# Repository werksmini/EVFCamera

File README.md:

# EVFCamera

A compact rangefinder-style digital camera built on a Raspberry Pi Zero 2 W and the Raspberry Pi HQ camera, with C/CS-mount lenses. You compose, review and change settings entirely through a 0.4" 1280×960 micro-OLED eye-level EVF.

## Hardware

| Part | Choice |
| --- | --- |
| Computer | Raspberry Pi Zero 2 W (hostname `EVFPi`) |
| Sensor | Raspberry Pi HQ camera (Sony IMX477) |
| Viewfinder | 0.4" 1280×960 HDMI micro-OLED, 12.5× eyepiece |
| Lenses | Fujinon-TV 9 mm f/1.4, 17 mm f/1.7 (C-mount) |
| Shutter | Alps SKRNPEE010 two-stage switch (bench: 6×6 tact switch) |
| Power | Adafruit bq25185 USB-C charger + 5 V boost, 1-cell Li-ion |
| Sensors | Deferred: MAX17048 fuel gauge, VCNL4040 eye sensor (I²C pins kept free) |

## Repository layout

| Folder | Contents |
| --- | --- |
| `bench/` | Standalone test scripts used while bringing up the hardware |
| `hardware/kicad/` | Footprints and PCB files |
| `docs/` | Roadmap and design notes |

| `evfcam/` | The camera app |
| `tests/` | Mode and control tests (run anywhere with the fake camera) |
| `tools/` | Helpers, e.g. `render_screens.py` draws every screen to PNG |

See [docs/roadmap.md](docs/roadmap.md) for the architecture and milestones.

## Setup on the Pi

Raspberry Pi OS Lite (64-bit), then:

```bash
sudo apt update && sudo apt full-upgrade -y
sudo raspi-config nonint do_i2c 0
sudo apt install -y python3-picamera2 --no-install-recommends
sudo apt install -y rpicam-apps-lite python3-pil python3-evdev python3-numpy python3-gpiozero i2c-tools git

mkdir -p ~/evfpi && cd ~/evfpi
python3 -m venv --system-site-packages .venv
source .venv/bin/activate
# later, for the deferred sensors:
# pip install adafruit-blinka adafruit-circuitpython-max1704x adafruit-circuitpython-vcnl4040
git clone https://github.com/werksmini/EVFCamera.git
```

Bench monitor (Waveshare 10.4" 1600×720, mounted upside down): add to the single line in `/boot/firmware/cmdline.txt`, then reboot:

```text
video=HDMI-A-1:1600x720,rotate=180
```

For the EVF instead: `video=HDMI-A-1:1280x960@60D`.

## Running the camera app

```bash
cd ~/evfpi/EVFCamera && git pull
python3 -m evfcam            # bench monitor (flipped, 960x720 window)
python3 -m evfcam --evf      # 0.4" EVF, 1280x960, not flipped
python3 -m evfcam --fake     # no camera: work on the UI anywhere
```

At the shutter press the screen goes dark with a white border and a red dot until the photo is saved, then live view returns with "SAVED". Review after the shot and the flash itself are in Menu > Display. In Shoot mode, the EV readout turns red with "MAX" when the exposure can't get any brighter.

Controls, typed in the SSH terminal or on a keyboard plugged into the Pi:

| Key | Camera control | Shoot | Magnify | Menu (page list) | Menu (inside a page) | Playback |
| --- | --- | --- | --- | --- | --- | --- |
| Space | Shutter (full) | Take photo | Take photo | Close | Close | Close |
| `h` | Shutter (half) | – | Close | Close | Close | Close |
| Enter | OK | Magnify 5× | 10×, then off | Open page | Step value / run action | – |
| ↑ ↓ | D-pad | ISO (Manual) | – | Move | Move | – |
| ← → | D-pad | – | – | ← close, → open | Change value | Browse |
| `m` | Menu | Open menu | Close | Close | Close menu | Close |
| `p` | Play | Playback | Playback | – | – | Close |
| `b` / Backspace | Back | Reset EV | Close | Close | Up to page list | Close |
| `[` `]` | Thumb wheel | EV (A) / shutter (S, M) | – | – | Change value | Browse |
| `q` | – | Quit | Quit | Quit | Quit | Quit |

Settings are saved to `~/.config/evfcam/settings.json` and come back after a restart.

The bench shutter button on GPIO 27 also works. Photos save to `~/evfpi/photos`.

Run the tests: `python3 tests/test_modes.py`

## Bench scripts

| Script | What it does |
| --- | --- |
| `bench/preview.py` | Live preview only |
| `bench/overlay.py` | Preview with exposure info and focus meter overlay |
| `bench/camera.py` | Overlay + shutter button on GPIO 27 (header pin 13, other leg to GND pin 14); saves full-res JPEGs to `~/evfpi/photos` |

```bash
cd ~/evfpi && source .venv/bin/activate
python3 EVFCamera/bench/camera.py
```

Set `FLIP = False` at the top of a script when using the EVF instead of the flipped bench monitor.

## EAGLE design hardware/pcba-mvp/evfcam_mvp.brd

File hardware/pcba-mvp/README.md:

# MVP main board (milled, single-sided)

`python3 make_pcba.py` places every part, routes the copper, checks clearances and writes:

| File | Use |
|---|---|
| `evfcam_mvp.sch`, `evfcam_mvp.brd` | Fusion Electronics (EAGLE 9 XML). Upload both together: File > Upload, or drag into the Data Panel |
| `gerber/evfcam_mvp-B_Cu.gbr` | Bottom copper, for isolation milling (FlatCAM, Carbide Copper, Fusion PCB CAM...) |
| `gerber/evfcam_mvp-Edge_Cuts.gbr` | Board outline and camera ribbon slot |
| `gerber/evfcam_mvp-PTH.drl`, `-NPTH.drl` | Pin holes (0.9 / 1.0 / 1.2 / 1.4 / 1.5 mm) and M2.5 screw holes (2.75 mm) |
| `preview.png` | Component side and the mirrored copper side |
| `fusion_dummy_board.py` | "Dummy board (print)" sketch: outline, cut-out and every hole, sizes as Fusion parameters |
| `fusion_sketches.py`, `layout.json` | Draws the layout into the Fusion "PCBA" design (`make_fusion_script.py` rebuilds it) |

Needs `numpy scipy scikit-image pillow shapely`.

## Board

Layout follows the "Skeleton" sketch in the Fusion PCBA design (105 x 55 mm, Pi in the bottom-left
corner), widened to 110.5 x 55 mm to make it routable on one side:

- **3 mm added on the left.** EN (charger to power switch) runs up the left edge outside the Pi's
  screws; the only gap at the end of the Pi header is taken by 5 V. The switch stays flush with the
  new left edge.
- **Cut-out, charger and gauge moved 2.5 mm right.** Five lanes (3V3, GND, SCL, SDA, 5V) climb between
  the Pi's top-right screw and the ribbon cut-out.

Copper on the back only (EAGLE layer 16). Signal traces 0.8 mm, power (5 V, battery, ground return)
1.2 mm, all at 0/45/90 degrees with no acute corners. The bus from under the Pi to the gauge and
charger is laid as fixed nested lanes; everything else is auto-routed, first at 0.4 mm clearance, then
each connection again at 0.65 mm where it fits without a detour. Closest copper: 0.5 mm (two bus lanes);
0.7 mm to edges, holes and the cut-out. No jumper wires.

Viewed from the component side (camera rear), X right, Y up, origin at the Pi's bottom-left corner:

| Part | Where | Notes |
|---|---|---|
| J1 Pi socket, 2x20 female | pin 1 at (8.37, 25.23); odd pins inner row | Pi plugs in upside down by its own pins |
| Pi screws | (3.5, 3.5) (61.5, 3.5) (3.5, 26.5) (61.5, 26.5) | |
| SW1 Fn, SW2 Menu | centres (21, 49), (33, 49) | Adafruit 3101 |
| SW3 Play | (33, 37) | 3101 |
| SW4 D-pad (504) | (47, 43) | Check the middle-pin offset with calipers before drilling |
| SW5 Shutter | (61, 49) | 3101 |
| SW6 power slide | pins at (-0.8, 44.7 / 46.7 / 48.7) | Actuator out of the left edge. Top pin = GND, so **slide up = off** |
| Ribbon cut-out | x 72-78, y 5-25 | Beside the Pi's camera connector |
| U1 charger 6106 | bottom-right corner, x 78.29-107.5; header y = 16.51 | USB-C over the right edge; 4 screws. Remove the screw terminal |
| U2 gauge 5580 | x 82.74-103.06, y 21.5-46.9; header column x = 85.28 | Fit only 4 header pins (VIN, GND, SCL, SDA) plus the 2 battery pins; 4 screws |

Battery: plugs into the charger's JST-PH socket as before. The board carries the charger's VBAT and
GND pins to the gauge's battery pins; leave the gauge's own battery connectors empty.

## Nets

| Net | From | To |
|---|---|---|
| +5V | charger 5V | Pi pins 2/4 |
| GND (power) | charger GND -> gauge battery GND; gauge GND | Pi pin 9 |
| VBAT | charger VBAT | gauge battery + |
| EN | charger EN | switch pin 2 (top pin = GND via Pi pin 6, so sliding up turns the boost off) |
| +3V3, SCL, SDA | Pi pins 17, 5, 3 | gauge VCC, SCL, SDA (gauge INT not used: the app polls) |
| FN, MENU, PLAY | GPIO 18 / 23 / 24 (pins 12 / 16 / 18) | buttons; grounds on pins 14 and 20 |
| UP, LEFT, DOWN | GPIO 25 / 8 / 7 (pins 22 / 24 / 26) | D-pad; common to pin 34 |
| RIGHT, OK | GPIO 16 / 20 (pins 36 / 38) | D-pad |
| SHUTTER | GPIO 21 (pin 40) | shutter; ground to pin 39 |

`evfcam/config.py` uses the same map.

## Milling and assembly

1. Mill the copper (bottom), drill, then cut the outline and slot. Most CAM tools mirror the bottom
   layer for you; check the result against the right half of `preview.png`.
2. Use nylon screws, standoffs and nuts in all twelve 2.75 mm holes: the nuts sit on the copper side,
   some over traces.
3. Solder low parts first: buttons, D-pad, slide switch, then the Pi socket, then the gauge and the
   charger through their own header pins.
4. Height: the Pi stack (socket plus Pi) stands about 10 mm; the 3101 buttons are 5.5 mm, so they need
   caps or the rear panel stepped.

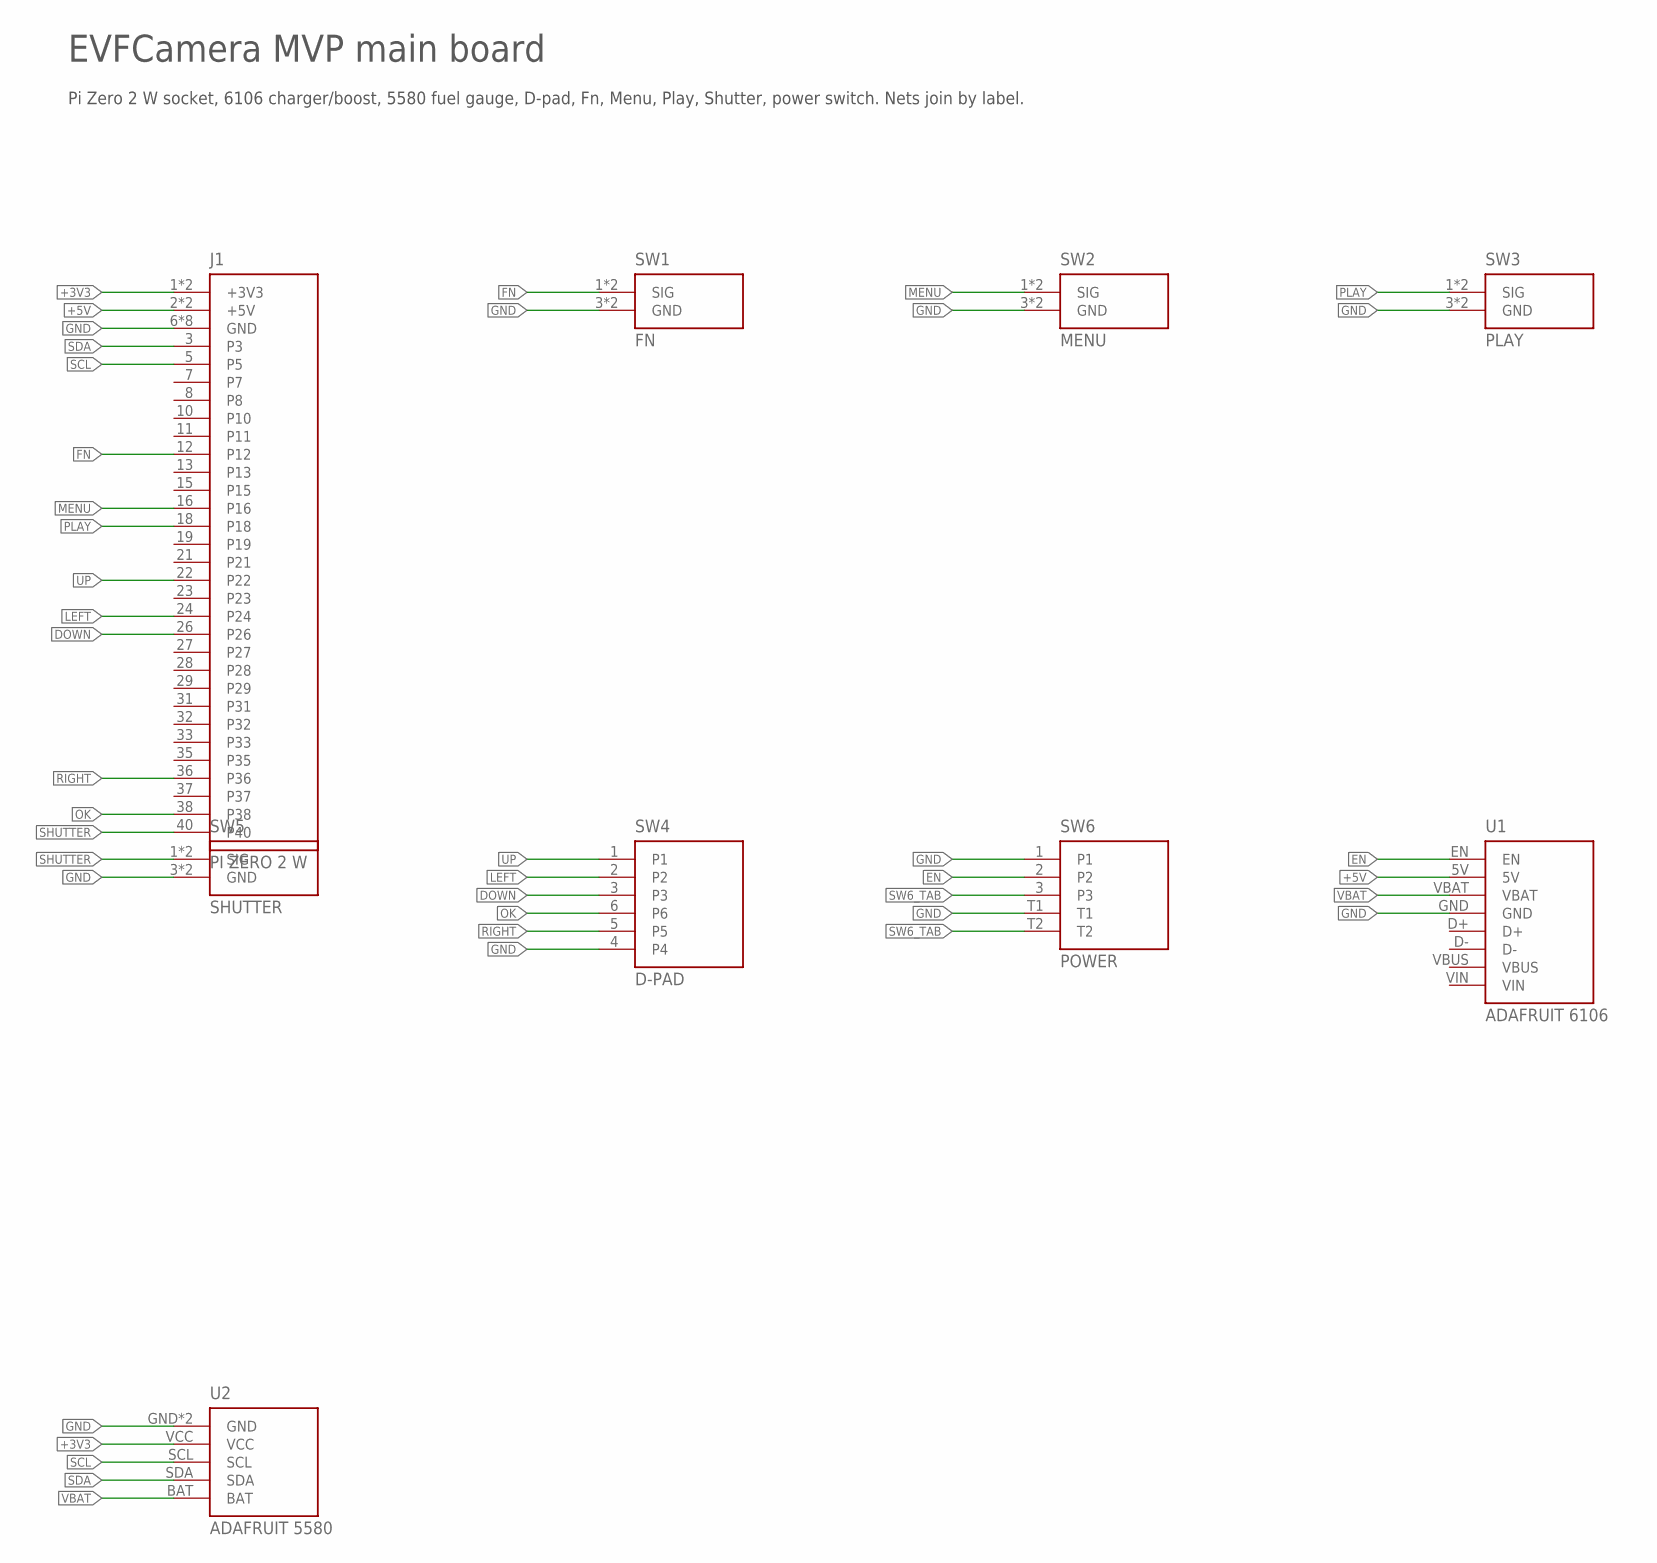
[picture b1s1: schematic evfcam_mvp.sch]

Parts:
J1: PI ZERO 2 W; J1_PKG
SW1: FN; SW1_PKG
SW2: MENU; SW2_PKG
SW3: PLAY; SW3_PKG
SW4: D-PAD; SW4_PKG
SW5: SHUTTER; SW5_PKG
SW6: POWER; SW6_PKG
U1: ADAFRUIT 6106; U1_PKG
U2: ADAFRUIT 5580; U2_PKG

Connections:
+3V3: J1.1 (+3V3), J1.17 (+3V3), U2.VCC
+5V: J1.2 (+5V), J1.4 (+5V), U1.5V
DOWN: J1.26, SW4.3
EN: SW6.2, U1.EN
FN: J1.12, SW1.1 (SIG), SW1.2 (SIG)
GND: J1.6 (GND), J1.9 (GND), J1.14 (GND), J1.20 (GND), J1.25 (GND), J1.30 (GND), J1.34 (GND), J1.39 (GND), SW1.3 (GND), SW1.4 (GND), SW2.3 (GND), SW2.4 (GND), SW3.3 (GND), SW3.4 (GND), SW4.4, SW5.3 (GND), SW5.4 (GND), SW6.1, SW6.T1, U1.GND, U2.BGND (GND), U2.GND
LEFT: J1.24, SW4.2
MENU: J1.16, SW2.1 (SIG), SW2.2 (SIG)
OK: J1.38, SW4.6
PLAY: J1.18, SW3.1 (SIG), SW3.2 (SIG)
RIGHT: J1.36, SW4.5
SCL: J1.5, U2.SCL
SDA: J1.3, U2.SDA
SHUTTER: J1.40, SW5.1 (SIG), SW5.2 (SIG)
SW6_TAB: SW6.3, SW6.T2
UP: J1.22, SW4.1
VBAT: U1.VBAT, U2.BAT

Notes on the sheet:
EVFCamera MVP main board
Pi Zero 2 W socket, 6106 charger/boost, 5580 fuel gauge, D-pad, Fn, Menu, Play, Shutter, power switch. Nets join by label.

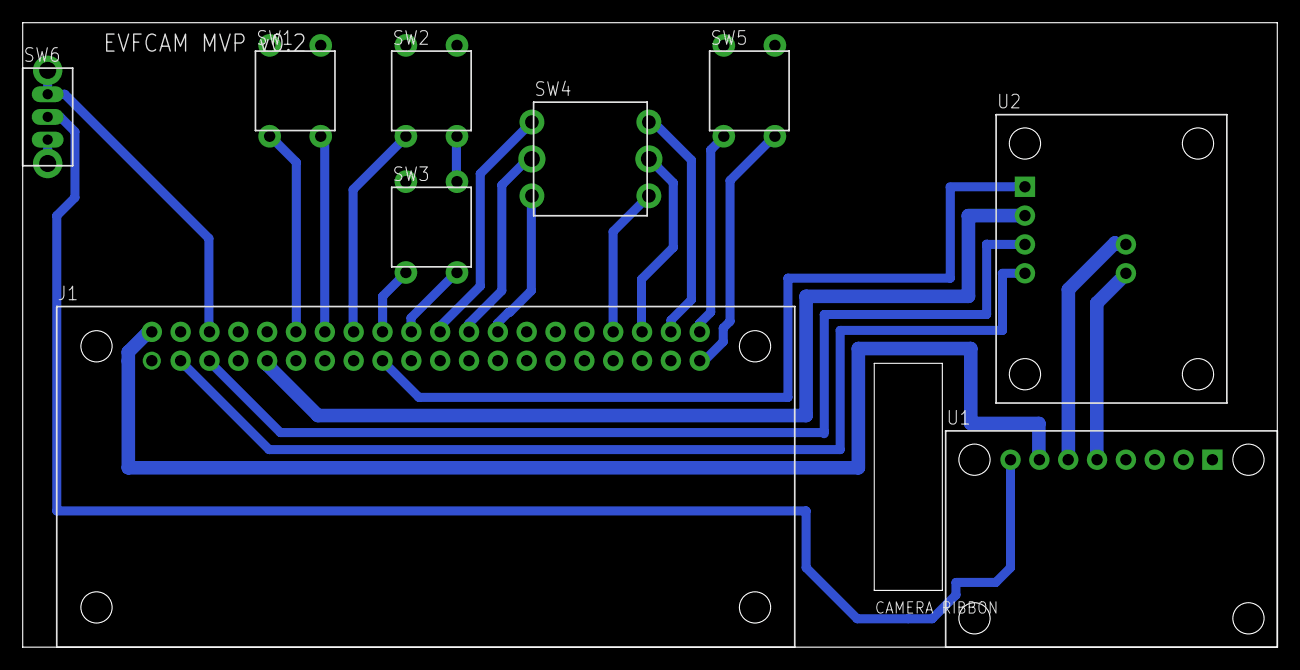
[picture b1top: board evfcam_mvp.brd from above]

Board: 2 copper layers, 110.5 x 55.0 mm, 9 parts (0 on the bottom side), 17 nets.

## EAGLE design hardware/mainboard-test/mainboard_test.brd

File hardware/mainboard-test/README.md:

# Test mainboard v0.1

First PCB for learning Fusion Electronics: connects the Pi Zero 2 W to the rear controls and to connectors for everything else. Placed but **not routed** — routing it in Fusion is the exercise.

| Ref | Part | Connects |
| --- | --- | --- |
| J1 | 2x20 header, 2.54 mm | Pi Zero 2 W (pin 1 lower-left; odd pins on the lower row, like the Pi seen from above) |
| SW1–SW5 | 6x6 mm through-hole tact switch | D-pad up, down, left, right, OK |
| SW6, SW7 | 6x6 mm tact switch | Back/Menu, Play |
| J2 | 1x2 header | 5 V in from the charger / PiSugar: 5V, GND |
| J3 | 1x3 header | Shutter (Alps SKRN): half, full, GND |
| J4 | 1x4 header | Thumb wheel: A, B, push, GND |
| J5 | 1x2 header | Front Fn button: FN, GND |
| J6 | 1x4 header | Top knob: A, B, push, GND |
| J7 | 1x5 header | I2C sensors (deferred): 3V3, GND, SDA, SCL, INT |

Nets and GPIOs: [netlist.csv](netlist.csv). They follow the project GPIO map; the thumb-wheel push uses GPIO 18.

**Switches are wired on diagonal pads (1 and 4)**, so they work whichever way round they're fitted.

**Milling-friendly:** single-sided, all through-hole, 1.8–2.0 mm pads on 1.0 mm holes, at least 1.5 mm copper between parts. Don't run traces between the 2.54 mm header pins (0.74 mm gap).

**Connecting the Pi:** easiest is a shrouded 2x20 box header for J1 and a 40-pin ribbon cable (like a T-Cobbler cable). If the Pi plugs straight onto this board instead, check which way up it sits first — a female header on the underside mirrors the pin order.

## Open in Fusion

1. Fusion: **File > Upload**, pick a project folder, select **both** `mainboard_test.sch` and `mainboard_test.brd`, Upload.
2. Leave **Create Electronics Design** ticked, OK.
3. Open the new Electronics Design; it holds the schematic and the PCB, linked.

## Regenerate

```bash
python3 make_mainboard.py   # writes .sch, .brd, netlist.csv
python3 preview.py          # writes mainboard_preview.png and prints the tightest spacing
```

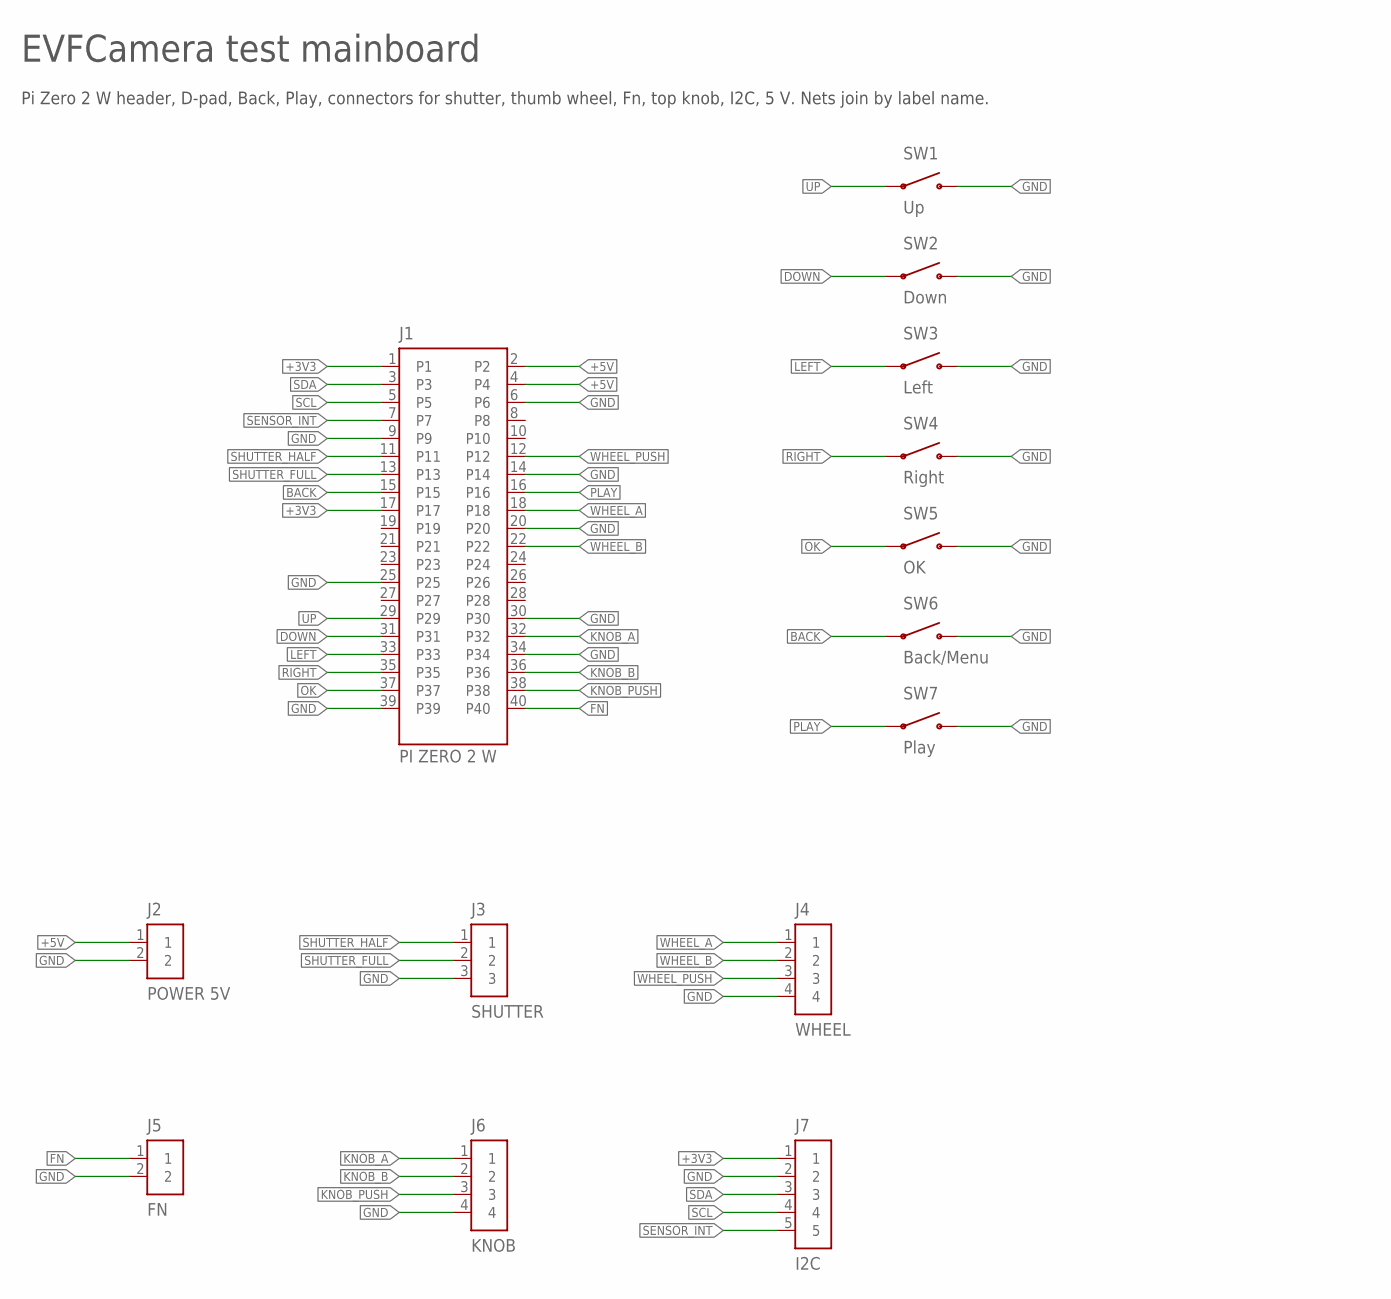
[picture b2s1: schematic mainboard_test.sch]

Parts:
J1: PI ZERO 2 W; PI_HEADER_2X20
J2: POWER 5V; HEADER_1X2
J3: SHUTTER; HEADER_1X3
J4: WHEEL; HEADER_1X4
J5: FN; HEADER_1X2
J6: KNOB; HEADER_1X4
J7: I2C; HEADER_1X5
SW1: Up; TACT_6X6_THT
SW2: Down; TACT_6X6_THT
SW3: Left; TACT_6X6_THT
SW4: Right; TACT_6X6_THT
SW5: OK; TACT_6X6_THT
SW6: Back/Menu; TACT_6X6_THT
SW7: Play; TACT_6X6_THT

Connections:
+3V3: J1.1, J1.17, J7.1
+5V: J1.2, J1.4, J2.1
BACK: J1.15, SW6.1 (A)
DOWN: J1.31, SW2.1 (A)
FN: J1.40, J5.1
GND: J1.6, J1.9, J1.14, J1.20, J1.25, J1.30, J1.34, J1.39, J2.2, J3.3, J4.4, J5.2, J6.4, J7.2, SW1.4 (B), SW2.4 (B), SW3.4 (B), SW4.4 (B), SW5.4 (B), SW6.4 (B), SW7.4 (B)
KNOB_A: J1.32, J6.1
KNOB_B: J1.36, J6.2
KNOB_PUSH: J1.38, J6.3
LEFT: J1.33, SW3.1 (A)
OK: J1.37, SW5.1 (A)
PLAY: J1.16, SW7.1 (A)
RIGHT: J1.35, SW4.1 (A)
SCL: J1.5, J7.4
SDA: J1.3, J7.3
SENSOR_INT: J1.7, J7.5
SHUTTER_FULL: J1.13, J3.2
SHUTTER_HALF: J1.11, J3.1
UP: J1.29, SW1.1 (A)
WHEEL_A: J1.18, J4.1
WHEEL_B: J1.22, J4.2
WHEEL_PUSH: J1.12, J4.3

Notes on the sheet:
EVFCamera test mainboard
Pi Zero 2 W header, D-pad, Back, Play, connectors for shutter, thumb wheel, Fn, top knob, I2C, 5 V. Nets join by label name.

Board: 1 copper layer, 14 parts (0 on the bottom side), 22 nets, no tracks yet.

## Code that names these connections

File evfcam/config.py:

"""Fixed settings for the hardware. Everything the user can change lives in settings.py."""
import os
from dataclasses import dataclass, field


@dataclass
class Config:
    # Where the preview window sits on the screen, and its size (= overlay size).
    # Bench: Waveshare 10.4" 1600x720, flipped 180 deg, 4:3 window in the middle.
    win_x: int = 320
    win_y: int = 0
    win_w: int = 960
    win_h: int = 720
    flip: bool = True                     # bench monitor is mounted upside down

    preview_size: tuple = (1280, 960)     # camera stream for the preview
    sensor_mode: tuple = (2028, 1520)     # full sensor, binned: preview framing = photo framing
    photos_dir: str = os.path.expanduser("~/evfpi/photos")
    # Physical buttons: BCM GPIO -> action name (evfcam.actions.A). Each switch closes to ground;
    # the Pi's internal pull-ups are used, so no resistors. MVP milled board: every button is on
    # the header's outer row (even pins), so the single-sided board breaks them all out on one side.
    # Left to right along the header (pin 1 at the SD-card end). Matches hardware/pcba-mvp.
    buttons: dict = field(default_factory=lambda: {
        18: "FN",           # pin 12  upper left; does what Setup > Fn button says (default Magnify)
        23: "MENU",         # pin 16
        24: "PLAY",         # pin 18  also Back inside the menu
        25: "UP",           # pin 22  D-pad (Adafruit 504)
        8: "LEFT",          # pin 24  (SPI CE0: keep SPI off)
        7: "DOWN",          # pin 26  (SPI CE1)
        16: "RIGHT",        # pin 36  (pin 34 next to it is the D-pad's ground)
        20: "OK",           # pin 38  D-pad press
        21: "SHUTTER_FULL",  # pin 40  right of the D-pad; single-stage for now
    })

    zoom_levels: tuple = (5, 10)          # Magnify mode steps
    in_focus: float = 0.95                # focus square goes green within 95% of peak sharpness
    peak_decay: float = 0.999             # how fast the "best focus" mark forgets
    redraw_s: float = 0.2                 # overlay refresh interval
    settings_path: str = os.path.expanduser("~/.config/evfcam/settings.json")



def bench() -> Config:
    return Config()


def evf() -> Config:
    """The 0.4" EVF: 1280x960, filled edge to edge, not flipped."""
    return Config(win_x=0, win_y=0, win_w=1280, win_h=960, flip=False)
